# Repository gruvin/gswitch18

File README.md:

# 18 Switch USB HID class 'Game Controller'

This project implements a USB 'Game Controller' with 18 switch (or button) interface ports, intended 
for use with PC flight simulators, to give additional inputs for external control panels.

No drivers required. 

# About This Project

A friend and I wanted a compact USB game controller interface, to provide at
least 10 switch inputs -- primarily for use with MS Flight Sim X and later, Condor Sailplane simulator.

See [`master` branch `README`](https://github.com/gruvin/gswitch18/blob/master/README.md) for some history.

This `smd` branch was created for the express purpose of making my first full PCB assembly purchase from [JLCPCB.com](https://jlcpcb.com). I have no use for these boards whatsoever but wanted to experience having my designs made into reality without touching a soldering iron.

KiCAD 3D Renders have imporved since I last looked!

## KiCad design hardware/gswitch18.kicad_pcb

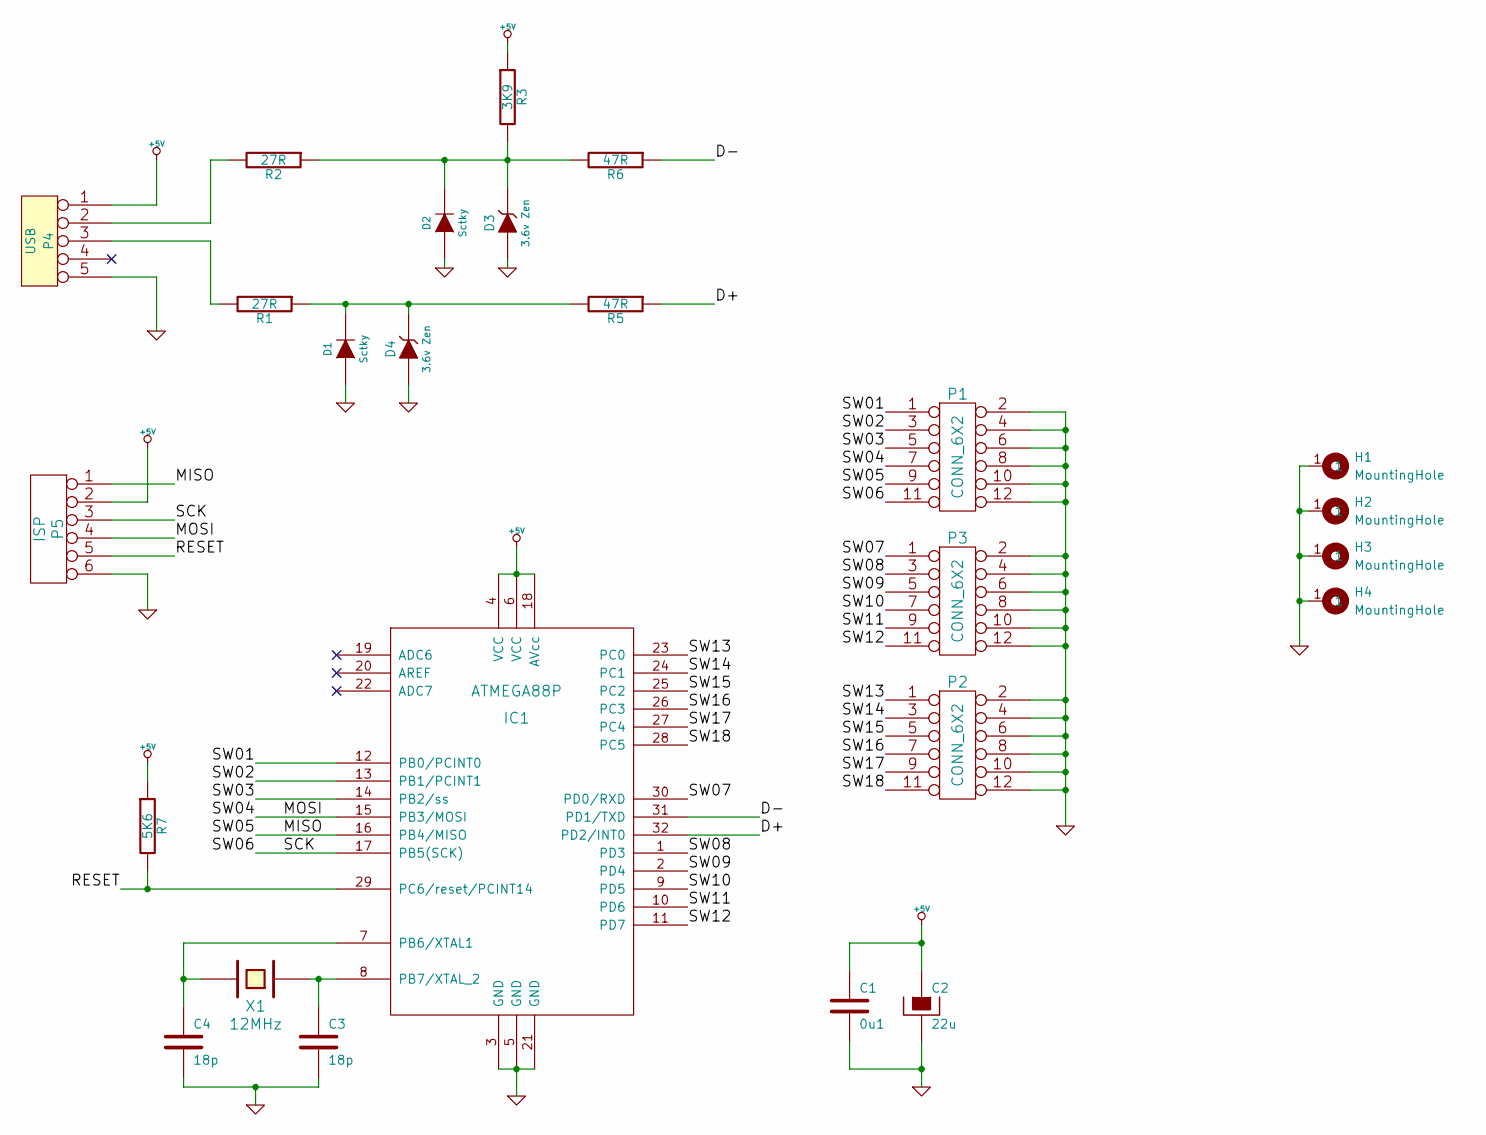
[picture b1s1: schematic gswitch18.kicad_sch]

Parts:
C1: 0u1; C_0603_1608Metric
C2: 22u; CP_EIA-3528-21_Kemet-B
C3, C4: 18p; C_0603_1608Metric
D1, D2: Sctky; D_SOD-523
D3, D4: 3.6v Zen; D_MiniMELF
H1, H2, H3, H4: MountingHole; MountingHole_3.2mm_M3_Pad_Via
IC1: ATMEGA88P; TQFP-32_7x7mm_P0.8mm
P1, P2, P3: CONN_6X2; PinHeader_2x06_P2.54mm_Vertical
P4: USB; USB_Mini-B_Wuerth_65100516121_Horizontal
P5: ISP; PinHeader_2x03_P2.54mm_Vertical
R1, R2: 27R; R_0603_1608Metric_Pad0.98x0.95mm_HandSolder
R3: 3K9; R_0603_1608Metric_Pad0.98x0.95mm_HandSolder
R5, R6: 47R; R_0603_1608Metric_Pad0.98x0.95mm_HandSolder
R7: 5K6; R_0603_1608Metric_Pad0.98x0.95mm_HandSolder
X1: 12MHz; Crystal_HC49-4H_Vertical

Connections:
+5V: C1.1, C2.1, IC1.4 (VCC), IC1.6 (VCC), IC1.18 (AVcc), P4.1, P5.2, R3.1, R7.1
/D+: IC1.32 (PD2/INT0), R5.1
/D-: IC1.31 (PD1/TXD), R6.1
/MISO: IC1.16 (PB4/MISO), P1.9, P5.1
/MOSI: IC1.15 (PB3/MOSI), P1.7, P5.4
/RESET: IC1.29 (PC6/reset/PCINT14), P5.5, R7.2
/SCK: IC1.17 (PB5(SCK)), P1.11, P5.3
/SW01: IC1.12 (PB0/PCINT0), P1.1
/SW02: IC1.13 (PB1/PCINT1), P1.3
/SW03: IC1.14 (PB2/ss), P1.5
/SW07: IC1.30 (PD0/RXD), P3.1
/SW08: IC1.1 (PD3), P3.3
/SW09: IC1.2 (PD4), P3.5
/SW10: IC1.9 (PD5), P3.7
/SW11: IC1.10 (PD6), P3.9
/SW12: IC1.11 (PD7), P3.11
/SW13: IC1.23 (PC0), P2.1
/SW14: IC1.24 (PC1), P2.3
/SW15: IC1.25 (PC2), P2.5
/SW16: IC1.26 (PC3), P2.7
/SW17: IC1.27 (PC4), P2.9
/SW18: IC1.28 (PC5), P2.11
GND: C1.2, C2.2, C3.2, C4.2, D1.1 (A), D2.1 (A), D3.1 (A), D4.1 (A), H1.1, H2.1, H3.1, H4.1, IC1.3 (GND), IC1.5 (GND), IC1.21 (GND), P1.2, P1.4, P1.6, P1.8, P1.10, P1.12, P2.2, P2.4, P2.6, P2.8, P2.10, P2.12, P3.2, P3.4, P3.6, P3.8, P3.10, P3.12, P4.5, P5.6
unnamed: D1.2 (K), D4.2 (K), R1.1, R5.2
unnamed: D2.2 (K), D3.2 (K), R2.1, R3.2, R6.2
unnamed: C4.1, IC1.7 (PB6/XTAL1), X1.2
unnamed: C3.1, IC1.8 (PB7/XTAL_2), X1.1
unnamed: P4.2, R2.2
unnamed: P4.3, R1.2

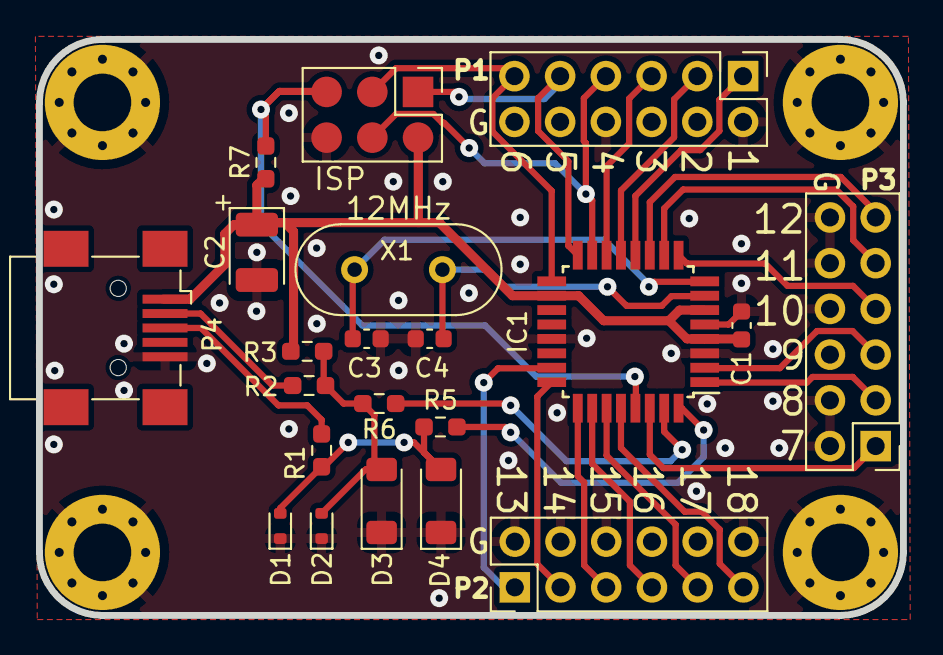
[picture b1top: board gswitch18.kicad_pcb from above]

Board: 2 copper layers, 48.0 x 32.0 mm, 25 parts (0 on the bottom side), 29 nets.

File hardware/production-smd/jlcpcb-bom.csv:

"Ref","JLCPCB","Qnty","Value","Cmp name","Footprint","Description","Vendor"
"C1, C2","C14663","2","0u1","C","Capacitor_SMD:C_0603_1608Metric","Unpolarized capacitor",""
"C3, C4","C107040","2","18p","C","Capacitor_SMD:C_0603_1608Metric","Unpolarized capacitor",""
"C5","C128254","1","10u tant.","C_Polarized","Capacitor_SMD:C_1206_3216Metric","Polarized capacitor",""
"D1, D2","C122862","2","Sctky","D_Schottky_1","Diode_SMD:D_SOD-523","Schottky diode",""
"D3, D4","C216708","2","3V6","D_Zener","Diode_SMD:D_SOD-123","Zener diode",""
"P1, P2, P3","C519164","3","JST GHS 1.25","Conn_01x07","Connector_JST:JST_GH_BM07B-GHS-TBT_1x07-1MP_P1.25mm_Vertical","Generic connector, single row, 01x07, script generated (kicad-library-utils/schlib/autogen/connector/)",""
"P4","C2681563","1","USB_B_Mini","USB_B_Mini","Connector_USB:USB_Mini-B_Wuerth_65100516121_Horizontal","USB Mini Type B connector",""
"R1, R2","C137753","2","27R","R","Resistor_SMD:R_0603_1608Metric","Resistor",""
"R3","C114616","1","3K9","R","Resistor_SMD:R_0603_1608Metric","Resistor",""
"R5, R6","C114623","2","47R","R","Resistor_SMD:R_0603_1608Metric","Resistor",""
"R7","C114627","1","5K6","R","Resistor_SMD:R_0603_1608Metric","Resistor",""
"U1","C8727","1","ATMEGA88P","ATMEGA48P","Package_QFP:TQFP-32_7x7mm_P0.8mm","",""
"X1","C258939","1","12MHz","Crystal_GND24","Crystal:Crystal_SMD_3225-4Pin_3.2x2.5mm","Four pin crystal, GND on pins 2 and 4",""

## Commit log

2012-09-08 Initial directory structure.
2012-09-08 Version 1.0 pre-production prototype.
    NOTE: Firmware is currently for ATmega2560 based G9X v4.2 RC controller board.
    (See gruvin9x.googlecode.com.) This was used for testing code function.
    I Will convert to the ATmega88P in due course -- probably about the
    time I receive the first prototype PCBs.
    SPECIAL THANKS to Objective Development for their excellent V-USB project
    (http://www.obdev.at/products/vusb/index.html) and to Joonas Pihlajamaa's
2012-09-24 Some Wings 3D work. Man that program is hard to use!
2012-09-25 Version 1.0 prototype tested working. [MILESTONE]
    Firmware modified for ATmega88p. Debugged and tested OK.
    (Old [main].c etc backed up to [etc]-2560.*)
    There were some errors with the PCB design around the
    USB socket ground pin and the front silk-screen switch
    number labels.
2012-09-25 Decided to match PCB design and code to prototype PCB silk screen, so as not to waste several boards.
    This should be the final v1.0 version now, since everything
    appears to be working and labelled correctly on the board.
    Yay \o/
    (Also added some wiki images with this commit.)
2012-09-25 Added wiki image
2012-09-25 Created wiki page through web user interface.
2012-09-26 Edited wiki page About through web user interface.
2012-09-26 Version bumped to v1.1.
    Improved component placement PDF (and made the file in assembly/ that,
    instead of an old schematic as before, in error. -/)
    Added PDF schematic in assembly/
2012-09-26 Made all ISP pads top-side only, so I dont have to fill them with solder each time it comes to loading firmware. ;-)
2012-09-26 Fixed fuse writing script so it actually works. Yay \o/
2012-09-26 Wings 6x2 pin arrays now replace KiCAD default versions.
2012-09-26 Minor 3D part perfectionism edit (some hard edges.)
2012-09-27 Corrected P2's 'G' label position.
2012-09-27 3D parts updated.
2012-09-27 Crazy-as 3D part upgrade! :-P
2012-09-27 Updated 3D package.
2012-09-28 3D shape update (again!)
2012-10-01 Oops! It's a good idea to set all the switch inputs to INPUT instead of output. Otherwise, strangely enough, the poor little ATmega get REALLY hot when you turn on several switches at once! Doh.
    Lysdexia strikes again.
2012-10-01 .elf files shouldn't be part of the repository. :-/
2012-10-04 Manually added polarity markers to diodes and cap in the parts placement PDF.
    Need to look into why the KiCAD modules are not correct for the zenors.
    Probably using a 1206POL instead of the actual diode footprint, if it even
    exists.
2012-10-04 PCB vias changed to 0.65mm with 0.4mm holes. This makes for better looking boards, especially when vias are tented, which is my preference for non-green mask boards.
2012-10-05 Production version 1.1 frozen in new archive folder.
    DigiKey BOM added.
2012-11-08 no comment
2012-11-08 BOM, finally completed. (NZ.element14.com only, at this stage.)
2013-04-25 Changed vendor address from codeandlife.com to gruvin9x.com
2013-04-27 A review of the shared PID usage file (USB-IDs-for-free.txt) revelaed that we were using the wrong VID/PID pair for a USB Joystock class HID device. Changed to 0x16c0/0x27dc, accordingly.
2013-04-27 Decided it best to move defines for VID/PID to main.c, so it's clearly visible in the main firmware code file.
2015-03-15 Migrating wiki contents from Google Code
2015-06-04 Added images
2015-06-04 Added archive folder, missed by Google Code export
2015-06-04 Deleted accidental .svn folder inclusion
2015-06-04 Deleted another .svn folder
2015-07-27 Minor README update.
2015-07-27 PCB updates. Wider tracks for CNC routing the board. (I used this board as my first test, to get things set up and working well.)
2015-07-28 Changed efuse to 0x01, wince that's what get read back during verify on an '88P. *shrug* Added wflash convenience script:
    [bash]$ . wflash
2016-11-25 Updated production files
2017-06-07 Update README.md
    The online store is no more. People will have to build their own or talk very nicely to me. :p
2022-04-24 Udate PCB for KiCAD v6
2022-04-25 v1.2 KiCAD 6 final changes
2022-04-25 added gitignore
2022-04-25 Added clippon™ CNC pendant switch matrix PCB for posterity.
2022-04-26 Futzing with fully SMD version. Don't like the JST PA connectors.
2022-04-26 smd milestone
2022-04-27 SMD: All JLCPCB part codes loaded. Other fixes.
2022-04-27 Added missing items to repo.
2022-04-27 MILESTONE: FIRST JLCPCB TEST ORDER
2022-04-27 USB_mini 3D model changed to KiCAD library version
2022-04-27 Updated to KiCAD v6. Bumped versionto v1.2 TH (through-hole). DEPRECATED; See smd branch.
2022-04-28 PCB keepout under xtal & tweaks (version bumped to v1.2.1)
2022-04-30 Schematic tidy-up (wasting time because why not?)
2022-05-06 Chnaged firmware to match new connectors on PCB v1.2
2022-05-06 Added #define to enable original PCB code generation (even though that's all unchanged in the master branch.)
2022-05-06 Comment typos from wy back
2022-05-07 Bug fixes. All working now. ('m88P lhfuse was way wrong. Had CLK/8 enabled! Weird.)
2022-05-07 Fixed fuse values. Never could have worked the way lfuse was. Weird.
2022-05-07 Added comments to gitignore
2022-05-09 Update README for smd branch
2022-06-08 Move the CNC 'gPendant' board to its repro. Cleaned up legacy files.
2023-12-09 updated to KiCAD 7.0
2023-12-09 Re-did update to KiCAD 7.0 (on PC)
2023-12-09 KiCAD v6.0 (mac)
2023-12-09 Corrected didoe 3D orientation
2023-12-11 v1.2 final tidy-up
